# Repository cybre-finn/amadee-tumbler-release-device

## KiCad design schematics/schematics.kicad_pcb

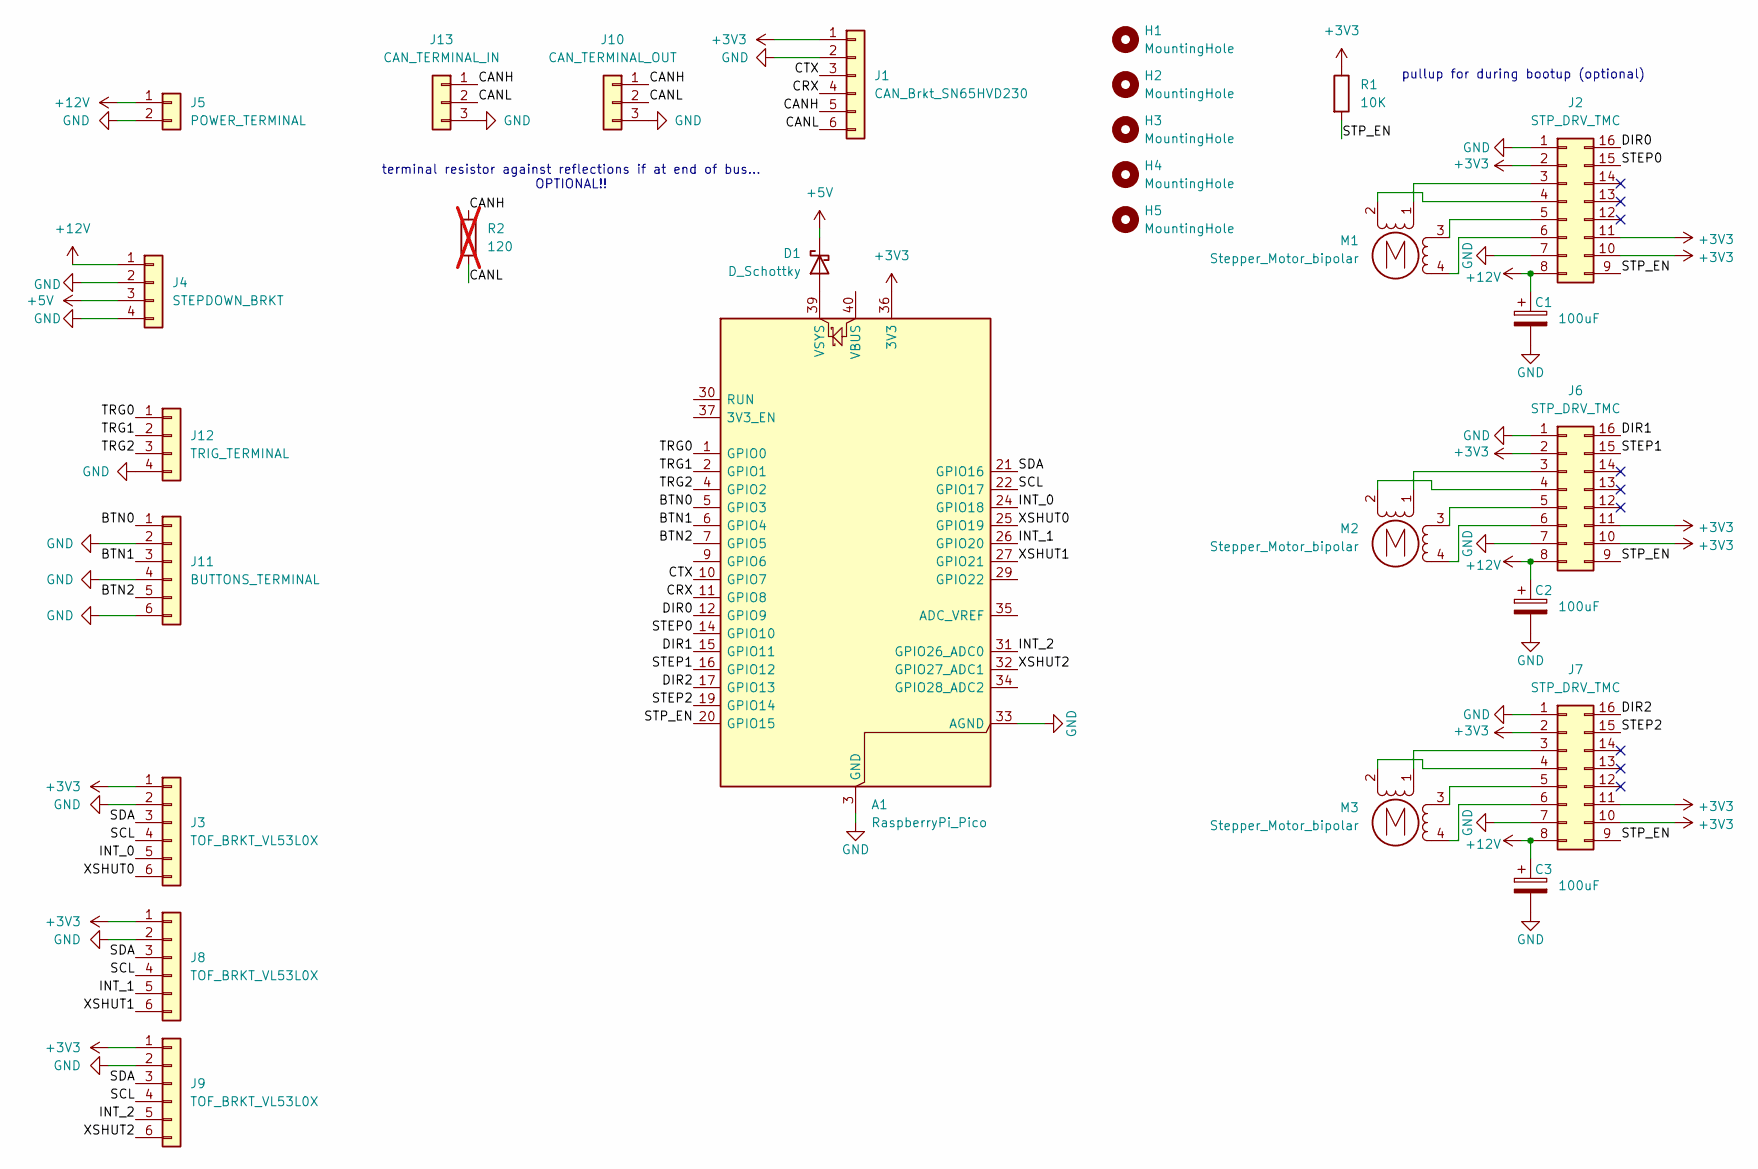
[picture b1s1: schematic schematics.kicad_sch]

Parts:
A1: RaspberryPi_Pico; RaspberryPi_Pico_Common_THT
C1, C2, C3: 100uF; CP_Radial_D8.0mm_P3.50mm
D1: D_Schottky; D_SMA
H1, H2, H3, H4, H5: MountingHole; MountingHole_3.2mm_M3
J1: CAN_Brkt_SN65HVD230; PinSocket_1x06_P2.54mm_Vertical
J2, J6, J7: STP_DRV_TMC; Pololu_Breakout-16_15.2x20.3mm
J3, J8, J9: TOF_BRKT_VL53L0X; TerminalBlock_Phoenix_MKDS-1,5-6_1x06_P5.00mm_Horizontal
J4: STEPDOWN_BRKT; BuckConverter
J5: POWER_TERMINAL; TerminalBlock_Phoenix_MKDS-1,5-2_1x02_P5.00mm_Horizontal
J10: CAN_TERMINAL_OUT; TerminalBlock_Phoenix_MKDS-1,5-3_1x03_P5.00mm_Horizontal
J11: BUTTONS_TERMINAL; TerminalBlock_Phoenix_MKDS-1,5-6_1x06_P5.00mm_Horizontal
J12: TRIG_TERMINAL; TerminalBlock_Phoenix_MKDS-1,5-4_1x04_P5.00mm_Horizontal
J13: CAN_TERMINAL_IN; TerminalBlock_Phoenix_MKDS-1,5-3_1x03_P5.00mm_Horizontal
M1, M2, M3: Stepper_Motor_bipolar; TerminalBlock_Phoenix_MKDS-1,5-4_1x04_P5.00mm_Horizontal
R1: 10K; R_0805_2012Metric
R2: 120; R_0805_2012Metric; not fitted

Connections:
+3V3: A1.36 (3V3), J1.1, J2.2, J2.10, J2.11, J3.1, J6.2, J6.10, J6.11, J7.2, J7.10, J7.11, J8.1, J9.1, R1.1
+5V: D1.1 (K), J4.3
+12V: C1.1, C2.1, C3.1, J2.8, J4.1, J5.1, J6.8, J7.8
/BTN0: A1.5 (GPIO3), J11.1
/BTN1: A1.6 (GPIO4), J11.3
/BTN2: A1.7 (GPIO5), J11.5
/CANH: J1.5, J10.1, J13.1, R2.1
/CANL: J1.6, J10.2, J13.2, R2.2
/CRX: A1.11 (GPIO8), J1.4
/CTX: A1.10 (GPIO7), J1.3
/DIR0: A1.12 (GPIO9), J2.16
/DIR1: A1.15 (GPIO11), J6.16
/DIR2: A1.17 (GPIO13), J7.16
/INT_0: A1.24 (GPIO18), J3.5
/INT_1: A1.26 (GPIO20), J8.5
/INT_2: A1.31 (GPIO26_ADC0), J9.5
/SCL: A1.22 (GPIO17), J3.4, J8.4, J9.4
/SDA: A1.21 (GPIO16), J3.3, J8.3, J9.3
/STEP0: A1.14 (GPIO10), J2.15
/STEP1: A1.16 (GPIO12), J6.15
/STEP2: A1.19 (GPIO14), J7.15
/STP_EN: A1.20 (GPIO15), J2.9, J6.9, J7.9, R1.2
/TRG0: A1.1 (GPIO0), J12.1
/TRG1: A1.2 (GPIO1), J12.2
/TRG2: A1.4 (GPIO2), J12.3
/XSHUT0: A1.25 (GPIO19), J3.6
/XSHUT1: A1.27 (GPIO21), J8.6
/XSHUT2: A1.32 (GPIO27_ADC1), J9.6
GND: A1.3 (GND), A1.8 (GND), A1.13 (GND), A1.18 (GND), A1.23 (GND), A1.28 (GND), A1.33 (AGND), A1.38 (GND), C1.2, C2.2, C3.2, J1.2, J2.1, J2.7, J3.2, J4.2, J4.4, J5.2, J6.1, J6.7, J7.1, J7.7, J8.2, J9.2, J10.3, J11.2, J11.4, J11.6, J12.4, J13.3
unnamed: A1.39 (VSYS), D1.2 (A)
unnamed: J2.3, M1.1
unnamed: J2.4, M1.2 (-_2)
unnamed: J2.5, M1.3
unnamed: J2.6, M1.4
unnamed: J6.3, M2.1
unnamed: J6.4, M2.2 (-_2)
unnamed: J6.5, M2.3
unnamed: J6.6, M2.4
unnamed: J7.3, M3.1
unnamed: J7.4, M3.2 (-_2)
unnamed: J7.5, M3.3
unnamed: J7.6, M3.4

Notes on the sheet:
terminal resistor against reflections if at end of bus... OPTIONAL!!
pullup for during bootup (optional)

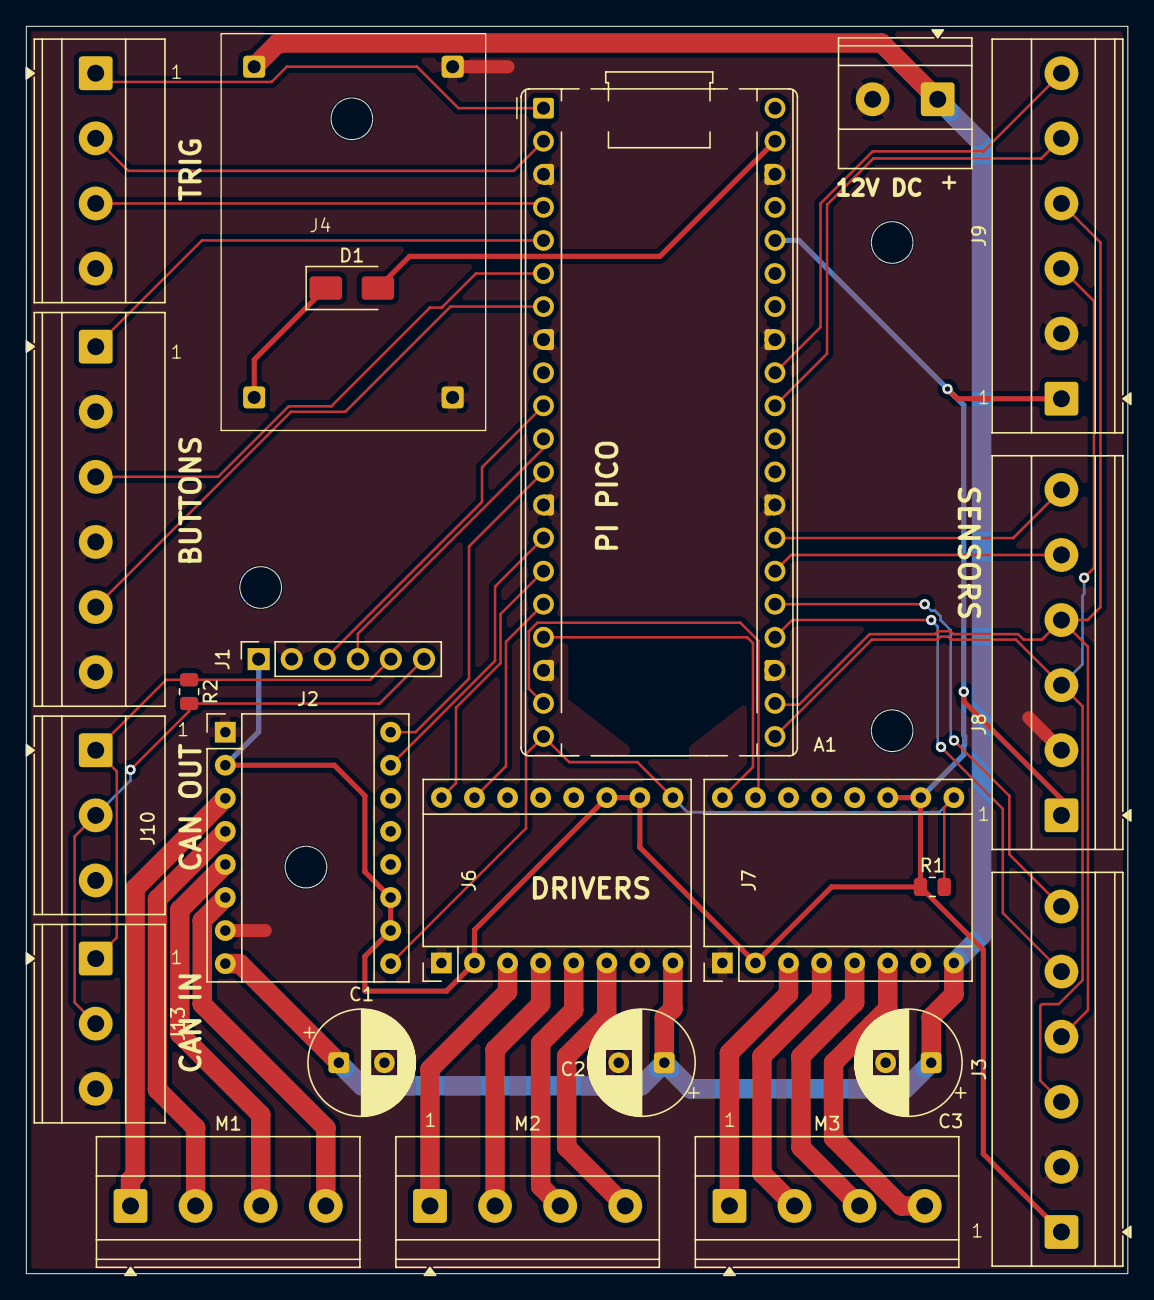
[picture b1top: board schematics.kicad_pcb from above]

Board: 2 copper layers, 84.6 x 95.8 mm, 28 parts (0 on the bottom side), 42 nets.
